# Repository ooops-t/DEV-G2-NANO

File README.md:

# G2 Nano Development Board
This repository houses the KiCad source files for the G2 Nano microcontroller development board.

The G2 Nano is powered by a record-breaking 1 GHz Arm Cortex-M7 processor, combining the performance of an application processor with real-time determinism. Purpose-built for robotics R&D, the board integrates dual-band Wi-Fi, an inertial measurement unit, and an on-board closed-loop motion controller.

## Overview
* This PCB was designed using KiCad 10 and its standard library of components.

* The KiCad project is contained within the `kicad/` directory and can be opened via the `kicad/DEV-G2-NANO.kicad_pro` file.

* All custom symbols and footprints are located in the `kicad/project_lib/` directory. The same directory houses the schematic page template.

## Features
### Performance
* 1 GHz Arm Cortex-M7 Microprocessor
* Double-Precision Floating Point Unit
* 2 MiB RAM (512 KiB Tightly Coupled)
* 8 MiB QSPI Flash Memory
* Cryptographic Acceleration (Including Random Number Generation)
* Two 32-Channel DMA Engines

### Peripherals
* Dual-Band Wi-Fi
* 6-Axis IMU (3-Axis Accelerometer; 3-Axis Gyroscope)
* 3-Axis Magnetometer
* 3-Axis Closed-Loop Motion Controller <!-- TODO: provide link to part -->
* Real-Time Clock (Optionally powered with a coin cell battery)
* Built-In Hardware Debugger

### Digital I/O
* 40 Digital GPIO
* 2 CAN/CAN-FD Interfaces
* 3 I2C Interfaces
* 2 SPI Interfaces
* 5 UART Interfaces

### Analog & Audio
* 10 Analog Inputs
* 2 I2S/TDM Interfaces
* S/PDIF Interface

## Using This Project
*This section is an informal summary of the license. For the full terms, see the `LICENSE.txt` file.*

The design files in this repository are licensed under the *CERN Open Hardware Licence Version 2 - Permissive* (CERN-OHL-P-2.0).

You are free to:
* Study these files and use them as inspiration or reference for your own independently created designs. As long as you are not copying, modifying, or redistributing the licensed design files, then you are not required to give attribution or license your design under the same terms.

* Copy, modify, and redistribute these files, including under different terms, provided you comply with the CERN-OHL-P-2.0 requirements.

**Trademarks:** No trademark rights are granted under this license. You may not use any trademarks or logos owned by Theta Machines LLC to endorse or promote products or services without prior written permission.

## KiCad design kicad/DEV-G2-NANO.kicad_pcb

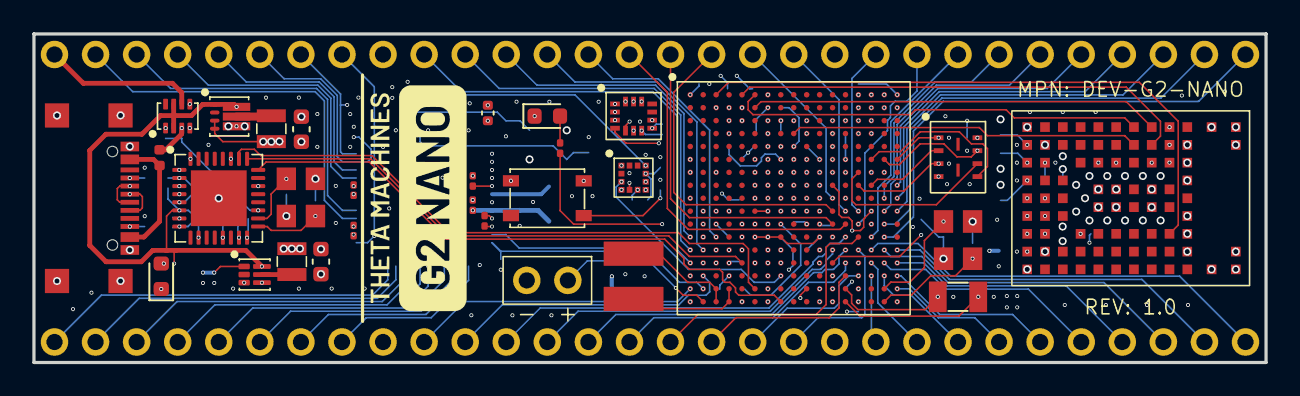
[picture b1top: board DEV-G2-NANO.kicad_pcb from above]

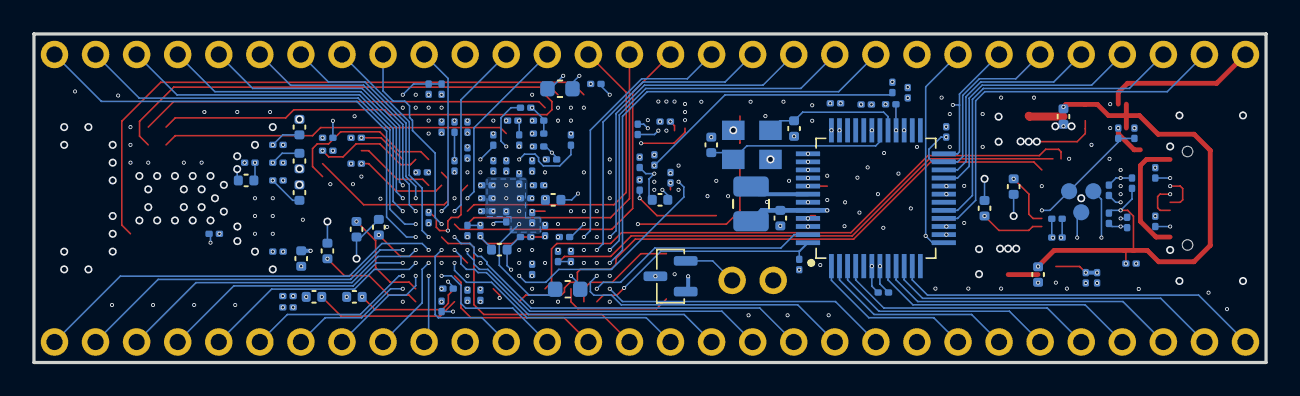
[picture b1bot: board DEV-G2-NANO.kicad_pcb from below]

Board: 6 copper layers, 76.2 x 20.3 mm, 140 parts (110 on the bottom side), 159 nets.

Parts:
C1, C2, C3, C7, C8, C11, C12, C13, C14, C18, C19, C21, C22, C23, C24, C25, C26, C29, C31, C32, C34, C39, C47, C54, C57, C63: 100nF; C_0201_0603Metric
C4, C5, C6, C9, C10, C15, C17, C20, C51, C76: 10μF; C_0402_1005Metric
C16, C67: 220nF; C_0201_0603Metric
C27, C28, C35, C36, C45, C46, C52, C53: 15pF; C_0402_1005Metric
C30, C33, C37, C40, C42, C43, C48, C55, C60, C61, C62, C64, C65, C68, C69, C70, C71, C72, C73, C74, C75: 2.2μF; C_0201_0603Metric
C38, C49, C50, C58, C59, C78: 1μF; C_0201_0603Metric
C41, C56, C77, C80: 22μF; C_0603_1608Metric
C44, C66, C79: 4.7μF; C_0402_1005Metric
D1, D3: RED; LED_0603_1608Metric
D2: BAT54C
FB1: 120Ω; L_0402_1005Metric
J1: Lower Bank; Header-1x30
J2: Upper Bank; Header-1x30
J3: USB C; UJ20-C-H-G-SMT-5-P16
J4: HIC SWD; TestPoints-3
J5: RTC Battery; Header-1x02
L1: 10μH; L_1008_2520Metric
L2: 4.7μH; SDCL1V4018
L3, L4: 470nH; L_0806
R1, R3, R4, R5, R6, R7, R8, R9, R10, R11, R13, R14, R15, R17, R18, R20, R21, R22, R23, R24, R25, R26, R27, R28, R29, R30, R32: 10kΩ; R_0201_0603Metric
R2: 2.2kΩ; R_0201_0603Metric
R12: 17.8kΩ; R_0201_0603Metric
R16, R19, R31: 5.1kΩ; R_0201_0603Metric
SW1: PTS815
U1: MIMXRT1171DVMAB
U2: MAYA-W166-00B
U3: LSM6DSV
U4: LIS2MDL
U5: RTMC-G2-4IQ48
U6: W25Q64JWUUIQ
U7: MKL26Z128VFM4
U8: LM66200
U9: TPS62086
U10: TPS62825
Y1: 8MHz; Crystal-4-Pin
Y2: 16MHz; Crystal-4-Pin
Y3: 24MHz; Crystal-4-Pin
Y4: 32.768kHz; Crystal-2-Pin

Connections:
+1V8: C1.1, C2.1, C3.1, C4.1, C5.1, C6.1, C11.1, C12.1, C13.1, C14.1, C15.1, C31.1, C32.1, C33.1, C34.1, C68.1, C69.1, C70.1, C71.1, C72.1, C73.1, C74.1, C75.1, C80.1, L4.2, R1.2, R7.2, R8.2, R9.2, R25.2, U1.D12 (NVCC_DISP1), U1.D14 (NVCC_SD1), U1.E7 (NVCC_DISP2), U1.F6 (NVCC_EMC1), U1.F7 (NVCC_EMC1), U1.G6 (NVCC_EMC1), U1.G13 (NVCC_SD2), U1.G16 (ADC_VREFH), U1.P7 (NVCC_LPSR), U2.A2 (1V8), U2.A6 (VIO_SD), U2.A8 (VIO), U3.5 (VDD_IO), U3.8 (VDD), U4.9 (VDD), U4.10 (VDD_IO), U6.8 (VCC), U7.7 (VDDA), U7.15 (VDD), U10.3 (FB)
+3V3: C7.1, C8.1, C9.1, C10.1, C19.1, C20.1, C21.1, C22.1, C23.1, C24.1, C25.1, C26.1, C39.1, C40.1, C41.1, C42.1, C43.1, C44.1, C77.1, D2.1, J1.20, J2.22, L3.2, R4.1, R5.1, R6.1, R32.2, U1.G12 (VDD_USB_3P3), U1.H6 (NVCC_EMC2), U1.J6 (NVCC_EMC2), U1.J13 (VDDA_ADC_3P3), U1.L5 (DCDC_IN_Q), U1.M5 (DCDC_IN), U1.M12 (NVCC_GPIO), U1.N5 (DCDC_IN), U1.R12 (VDD_LPSR_IN), U2.A7 (3V3), U2.B7 (3V3), U5.7 (VDD), U5.15 (VDD), U5.20 (VDD), U5.28 (VDD), U5.36 (VDD), U5.41 (BUCK_IN), U5.46 (VDD), U9.3 (FB), U9.4 (VOS)
+5V: C29.1, C30.1, C76.1, C79.1, R31.1, U7.6 (VREGIN), U8.2 (VOUT), U8.7 (VOUT), U9.1 (EN), U9.7 (VIN), U10.6 (VIN)
E1_A: J1.6, U5.3 (E1_A)
E1_B: J1.5, U5.4 (E1_B)
E2_A: J1.2, U5.10 (E2_A)
E2_B: J1.1, U5.11 (E2_B)
E3_A: J2.29, U5.16 (E3_A)
E3_B: J2.28, U5.17 (E3_B)
FAULT_IN: J2.24, U1.M2 (GPIO_EMC_B2_12), U5.24 (FAULT_IN)
FAULT_OUT: J2.25, R6.2, U1.N3 (GPIO_EMC_B2_18), U5.23 (FAULT_OUT)
GND: C1.2, C2.2, C3.2, C4.2, C5.2, C6.2, C7.2, C8.2, C9.2, C10.2, C11.2, C12.2, C13.2, C14.2, C15.2, C16.2, C17.2, C18.2, C19.2, C20.2, C21.2, C22.2, C23.2, C24.2, C25.2, C26.2, C27.1, C28.1, C29.2, C30.2, C31.2, C32.2, C33.2, C34.2, C35.1, C36.1, C37.2, C38.2, C39.2, C40.2, C41.2, C42.2, C43.2, C44.2, C45.1, C46.1, C47.2, C48.2, C49.2, C50.2, C51.2, C52.1, C53.1, C54.2, C55.2, C56.2, C57.2, C58.2, C59.2, C60.2, C61.2, C62.2, C63.2, C64.2, C65.2, C66.2, C67.2, C68.2, C69.2, C70.2, C71.2, C72.2, C73.2, C74.2, C75.2, C76.2, C77.2, C78.2, C79.2, C80.2, D1.1 (K), D3.1 (K), J1.9, J2.11, J3.A1_B12 (GND), J3.B1_A12 (GND), J3.S1 (SHIELD), J5.2, R3.2, R10.2, R11.2, R13.2, R14.2, R15.2, R16.2, R17.1, R18.2, R19.2, R20.2, R21.2, R22.2, R23.2, R24.2, R26.2, R27.1, R28.2, R29.2, R30.2, SW1.1, U1.A1 (VSS), U1.A17 (VSS), U1.B7 (VSS), U1.C8 (VSS), U1.C10 (VSS), U1.C12 (VSS), U1.C14 (VSS), U1.D4 (VSS), U1.F11 (VSS), U1.F12 (VSS), U1.F13 (VSS), U1.G3 (VSS), U1.G7 (VSS), U1.G8 (VSS), U1.G9 (VSS), U1.G10 (VSS), U1.G11 (VSS), U1.G15 (VSS), U1.H7 (VSS), U1.H11 (VSS), U1.J7 (VSS), U1.J11 (VSS), U1.K6 (DCDC_GND), U1.K7 (DCDC_GND), U1.K11 (VSS), U1.L3 (VSS), U1.L6 (DCDC_GND), U1.L10 (VSS), U1.L11 (VSS), U1.L15 (VSS), U1.P4 (VSS), U1.P14 (VSS), U1.R4 (VSS), U1.R7 (VSS), U1.T11 (TEST_MODE), U1.T12 (VSS), U1.U1 (VSS), U1.U17 (VSS), U2.A1 (GND), U2.A9 (GND), U2.B2 (GND), U2.B8 (GND), U2.E4 (GND), U2.E5 (GND), U2.F4 (GND), U2.F5 (GND), U2.H4 (GND), U2.H5 (GND), U2.K2 (GND), U2.K3 (GND), U2.K4 (GND), U2.K6 (GND), U2.K7 (GND), U2.K8 (GND), U2.L1 (GND), U2.L9 (GND), U2.M1 (GND), U2.M2 (GND), U2.M8 (GND), U2.M9 (GND), U3.2 (SDx), U3.3 (SCx), U3.6 (GND), U3.7 (GND), U4.6 (GND), U4.8 (GND), U5.6 (GND), U5.14 (GND), U5.19 (GND), U5.27 (GND), U5.35 (GND), U5.43 (BUCK_GND), U5.45 (GND), U6.4 (GND), U7.2 (VSS), U7.8 (VSSA), U7.16 (VSS), U7.33 (EPAD), U8.1 (GND), U8.4 (~ON), U8.5 (GND), U9.5 (GND), U10.4 (GND), Y1.2 (GND), Y1.4 (GND), Y2.2 (GND), Y2.4 (GND), Y3.2 (GND), Y3.4 (GND)
M1_A: J1.8, U5.1 (M1_A)
M1_B: J1.7, U5.2 (M1_B)
M2_A: J1.4, U5.8 (M2_A)
M2_B: J1.3, U5.9 (M2_B)
M3_A: J2.27, U5.21 (M3_A)
M3_B: J2.26, U5.22 (M3_B)
unnamed: D1.2 (A), R2.1
unnamed: D3.2 (A), R31.2
unnamed: FB1.2, J3.A4_B9 (VBUS), J3.B4_A9 (VBUS)
unnamed: J1.10, U1.T1 (GPIO_EMC_B2_06)
unnamed: J1.11, U1.R2 (GPIO_EMC_B2_10)
unnamed: J1.12, U1.M13 (GPIO_AD_04)
unnamed: J1.13, U1.N12 (GPIO_AD_00)
unnamed: J1.14, U1.N13 (GPIO_AD_06)
unnamed: J1.15, U1.P13 (GPIO_AD_05)
unnamed: J1.16, U1.M14 (GPIO_AD_15)
unnamed: J1.17, U1.R13 (GPIO_AD_02)
unnamed: J1.18, U1.R14 (GPIO_AD_01)
unnamed: J1.19, U1.N14 (GPIO_AD_14)
unnamed: J1.21, U1.R15 (GPIO_AD_08)
unnamed: J1.22, U1.P15 (GPIO_AD_03)
unnamed: J1.23, U1.R16 (GPIO_AD_09)
unnamed: J1.24, U1.T17 (GPIO_AD_07)
unnamed: J1.25, U1.R17 (GPIO_AD_10)
unnamed: J1.26, U1.P16 (GPIO_AD_11)
unnamed: J1.27, U1.P17 (GPIO_AD_12)
unnamed: J1.28, U1.N16 (GPIO_AD_27)
unnamed: J1.29, U1.N17 (GPIO_AD_16)
unnamed: J1.30, U1.N15 (GPIO_AD_17)
unnamed: J2.1, U1.M16 (GPIO_AD_18)
unnamed: J2.2, U1.L16 (GPIO_AD_19)
unnamed: J2.3, U1.K17 (GPIO_AD_30)
unnamed: J2.4, U1.J17 (GPIO_AD_31)
unnamed: J2.5, U1.H17 (GPIO_AD_33)
unnamed: J2.6, U1.K16 (GPIO_AD_32)
unnamed: J2.7, U1.J16 (GPIO_AD_34)
unnamed: J2.8, U1.M15 (GPIO_AD_25)
unnamed: J2.9, U1.L14 (GPIO_AD_26)
unnamed: J2.10, U1.K14 (GPIO_AD_21)
unnamed: J2.12, U1.K13 (GPIO_AD_20)
unnamed: J2.13, U1.J12 (GPIO_AD_23)
unnamed: J2.14, U1.K12 (GPIO_AD_22)
unnamed: J2.15, U1.L12 (GPIO_AD_13)
unnamed: J2.16, U1.L13 (GPIO_AD_24)
unnamed: J2.17, U1.M3 (GPIO_EMC_B2_07)
unnamed: J2.18, U1.N2 (GPIO_EMC_B2_09)
unnamed: J2.19, U1.M1 (GPIO_EMC_B2_04)
unnamed: J2.20, U1.N1 (GPIO_EMC_B2_05)
unnamed: J2.21, U1.P1 (GPIO_EMC_B2_08)
unnamed: J3.A5 (CC1), R16.1
unnamed: J3.B5 (CC2), R19.1
unnamed: J4.1, R12.1, R17.2, U7.19 (PTA20)
unnamed: J4.2, U7.10 (PTA0)
unnamed: J4.3, U7.13 (PTA3)
unnamed: D2.2, J5.1
unnamed: L2.1, U1.T4 (DCDC_LN), U1.U4 (DCDC_LN)
unnamed: L2.2, U1.T3 (DCDC_LP), U1.U3 (DCDC_LP)
unnamed: R28.1, U1.N4 (DCDC_MODE)
unnamed: C62.1, C63.1, U1.U11 (NVCC_SNVS), U1.U14 (VDD_SNVS_ANA)
unnamed: C52.2, U1.T13 (RTC_XTALI), Y4.2
unnamed: C53.2, U1.U13 (RTC_XTALO), Y4.1
unnamed: C64.1, U1.N11 (VDDA_1P0)
unnamed: C66.1, U1.P12 (VDD_LPSR_ANA)
unnamed: C65.1, U1.P11 (VDD_LPSR_DIG)
unnamed: R30.1, U1.F10 (VDD_MIPI_1P0)
unnamed: R29.1, U1.F9 (VDD_MIPI_1P8)
unnamed: C67.1, U1.T14 (VDD_SNVS_DIG)
unnamed: C38.1, D2.3, U1.U12 (VDD_SNVS_IN)
unnamed: C46.2, U1.U16 (XTALI), Y3.3
unnamed: C45.2, U1.T16 (XTALO), Y3.1
unnamed: R10.1, U1.D10 (GPIO_DISP_B1_06)
unnamed: R11.1, U1.E12 (GPIO_DISP_B1_07)
unnamed: R13.1, U1.A15 (GPIO_DISP_B1_08)
unnamed: R14.1, U1.C13 (GPIO_DISP_B1_09)
unnamed: R15.1, U1.B14 (GPIO_DISP_B1_10)
unnamed: R18.1, U1.A14 (GPIO_DISP_B1_11)
unnamed: R20.1, U1.E8 (GPIO_DISP_B2_00)
unnamed: R21.1, U1.F8 (GPIO_DISP_B2_01)
unnamed: R22.1, U1.E9 (GPIO_DISP_B2_02)
unnamed: R23.1, U1.D7 (GPIO_DISP_B2_03)
unnamed: R24.1, U1.C7 (GPIO_DISP_B2_04)
unnamed: R26.1, U1.C9 (GPIO_DISP_B2_05)
unnamed: R27.2, U1.P6 (GPIO_LPSR_02), U7.32 (PTD7)
unnamed: R25.1, U1.T7 (GPIO_LPSR_03), U7.1 (PTE0)
unnamed: U1.U8 (GPIO_LPSR_08), U7.24 (PTC3)
unnamed: U1.P5 (GPIO_LPSR_09), U7.25 (PTC4)
unnamed: U1.T6 (GPIO_LPSR_14), U7.26 (PTC5)
unnamed: U1.U7 (GPIO_LPSR_15), U7.27 (PTC6)
unnamed: R9.1, U1.F17 (GPIO_SD_B2_06), U6.1 (~CS)
unnamed: U1.G14 (GPIO_SD_B2_07), U6.6 (CLK)
unnamed: U1.F15 (GPIO_SD_B2_08), U6.5 (DI/IO_{0})
unnamed: U1.H15 (GPIO_SD_B2_09), U6.2 (DO/IO_{1})
unnamed: R8.1, U1.H14 (GPIO_SD_B2_10), U6.3 (~WP/IO_{2})
unnamed: R7.1, U1.F16 (GPIO_SD_B2_11), U6.7 (~HOLD/~RESET/IO_{3})
unnamed: U1.T10 (POR_B), U7.22 (PTC1)
unnamed: U1.B5 (GPIO_DISP_B2_08), U2.J7 (BT_RESET)
unnamed: U1.D9 (GPIO_DISP_B2_10), U2.G8 (UART_SIN)
unnamed: U1.A6 (GPIO_DISP_B2_11), U2.G9 (UART_SOUT)
unnamed: U1.B6 (GPIO_DISP_B2_12), U2.H9 (UART_RTSn)
unnamed: U1.A5 (GPIO_DISP_B2_13), U2.H8 (UART_CTSn)
unnamed: U1.A7 (GPIO_DISP_B2_14), U2.H7 (WLAN_RESET)
unnamed: U1.A3 (GPIO_EMC_B1_09), U2.J3 (PDn)
unnamed: U1.C5 (GPIO_EMC_B1_12), U2.E7 (BT_WAKE_HOST)
unnamed: U1.B3 (GPIO_EMC_B1_17), U2.J9 (BT_DEV_WAKE)
unnamed: U1.B4 (GPIO_EMC_B1_18), U2.J8 (WLAN_DEV_WAKE)
unnamed: U1.C4 (GPIO_EMC_B1_19), U2.F7 (WLAN_WAKE_HOST)
unnamed: U1.F1 (GPIO_EMC_B1_35), U3.9 (INT2)
unnamed: U1.G1 (GPIO_EMC_B1_36), U3.4 (INT1)
unnamed: R1.1, SW1.2, U1.J1 (GPIO_EMC_B1_38)
unnamed: U1.K2 (GPIO_EMC_B2_00), U5.38 (SCLK)
unnamed: U1.K4 (GPIO_EMC_B2_01), U5.37 (CS_N)
unnamed: U1.K3 (GPIO_EMC_B2_02), U5.39 (DI)
unnamed: U1.R1 (GPIO_EMC_B2_03), U5.40 (DO)
unnamed: R2.2, U1.L2 (GPIO_EMC_B2_15)
unnamed: U1.T2 (GPIO_EMC_B2_17), U5.47 (INTER)
unnamed: R4.2, U1.U2 (GPIO_EMC_B2_19), U5.48 (RESET_N)
unnamed: U1.N7 (GPIO_LPSR_04), U3.14 (SDI), U4.4 (SDI)
unnamed: U1.N8 (GPIO_LPSR_05), U3.1 (SDO), U4.7 (SDO)
unnamed: U1.P8 (GPIO_LPSR_06), U3.12 (CS)
unnamed: U1.R8 (GPIO_LPSR_07), U4.3 (CS)
unnamed: U1.U5 (GPIO_LPSR_12), U3.13 (SCL), U4.1 (SPC)
unnamed: U1.B16 (GPIO_SD_B1_00), U2.B4 (SD_CMD)
unnamed: U1.D15 (GPIO_SD_B1_01), U2.A4 (SD_CLK)
unnamed: U1.C15 (GPIO_SD_B1_02), U2.B3 (SD_DAT[0])
unnamed: U1.B17 (GPIO_SD_B1_03), U2.A3 (SD_DAT[1])
unnamed: U1.B15 (GPIO_SD_B1_04), U2.B5 (SD_DAT[2])
unnamed: U1.A16 (GPIO_SD_B1_05), U2.A5 (SD_DAT[3])
unnamed: R3.1, U2.D3 (CONFIG[0])
unnamed: C16.1, U4.5 (C1)
unnamed: L1.2, U5.42 (BUCK_SW)
unnamed: R5.2, U5.31 (ENABLE)
unnamed: C28.2, U5.30 (OSCI), Y1.3
unnamed: C27.2, U5.29 (OSCO), Y1.1
unnamed: C35.2, U7.17 (PTA18), Y2.1
unnamed: C36.2, U7.18 (PTA19), Y2.3
unnamed: J3.A7 (D-), J3.B7 (D-), U7.4 (USB0_DM)
unnamed: J3.A6 (D+), J3.B6 (D+), U7.3 (USB0_DP)
unnamed: C37.1, U7.5 (VOUT33)
unnamed: L3.1, U9.6 (SW)
unnamed: L4.1, U10.5 (SW)
RC_DELAY: C78.1, R32.1, U1.P3 (DCDC_PSWITCH), U10.1 (EN)
UPDATE: J2.23, U1.P2 (GPIO_EMC_B2_16), U5.13 (UPDATE)
V_{BUCK}: C17.1, C18.1, L1.1, U5.44 (VDD_CORE)
V_{DCDC_ANA}: C47.1, C48.1, C49.1, C50.1, C51.1, U1.H12 (VDD_USB_1P8), U1.K15 (VDDA_ADC_1P8), U1.M6 (DCDC_ANA_SENSE), U1.M7 (DCDC_ANA), U1.M8 (DCDC_ANA), U1.M11 (VDDA_1P8_IN)
V_{DCDC_DIG}: C54.1, C55.1, C56.1, C57.1, C58.1, C59.1, C60.1, C61.1, U1.H8 (VDD_SOC_IN), U1.H9 (VDD_SOC_IN), U1.H10 (VDD_SOC_IN), U1.J8 (VDD_SOC_IN), U1.J9 (VDD_SOC_IN), U1.J10 (VDD_SOC_IN), U1.K8 (DCDC_DIG), U1.K9 (DCDC_DIG), U1.K10 (VDD_SOC_IN), U1.L7 (DCDC_DIG_SENSE), U1.L8 (DCDC_DIG)
V_{IN}: J2.30, U8.6 (VIN2)
V_{USB}: FB1.1, R12.2, U8.3 (VIN1)
